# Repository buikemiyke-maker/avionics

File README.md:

# avionics
simple flight controller
the BOM can be found in the production folder
and also the code in the code folder
This took around a month and Im pretty unsure about some of my work so feel free to ask for any tweaks and Ill try to deliver asap 
The bills for parts I need, I will be uploading this onto the blueprint site aswell

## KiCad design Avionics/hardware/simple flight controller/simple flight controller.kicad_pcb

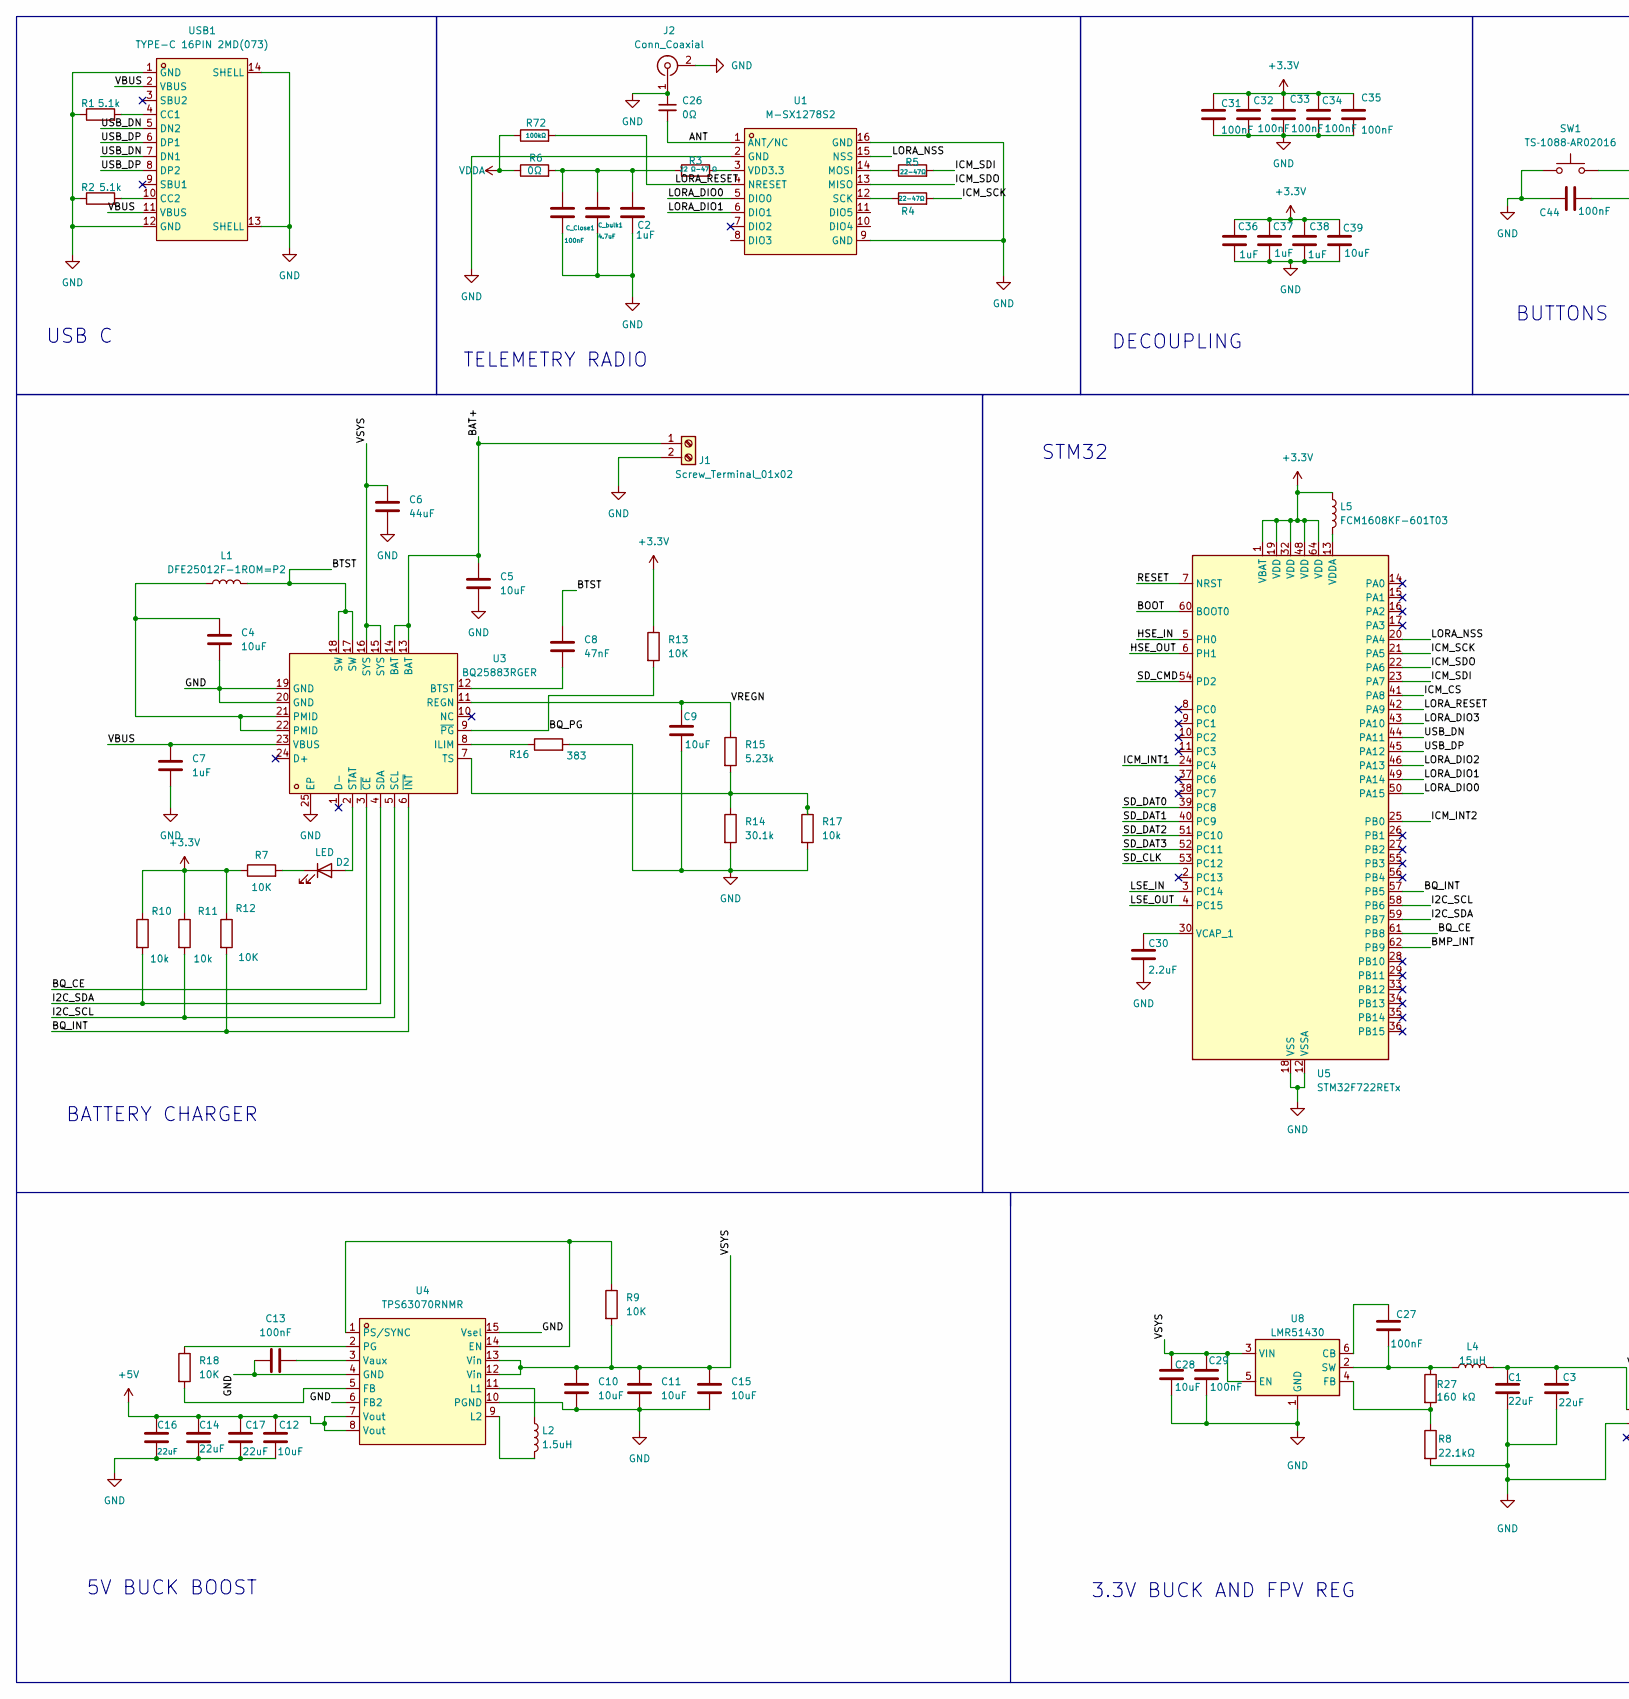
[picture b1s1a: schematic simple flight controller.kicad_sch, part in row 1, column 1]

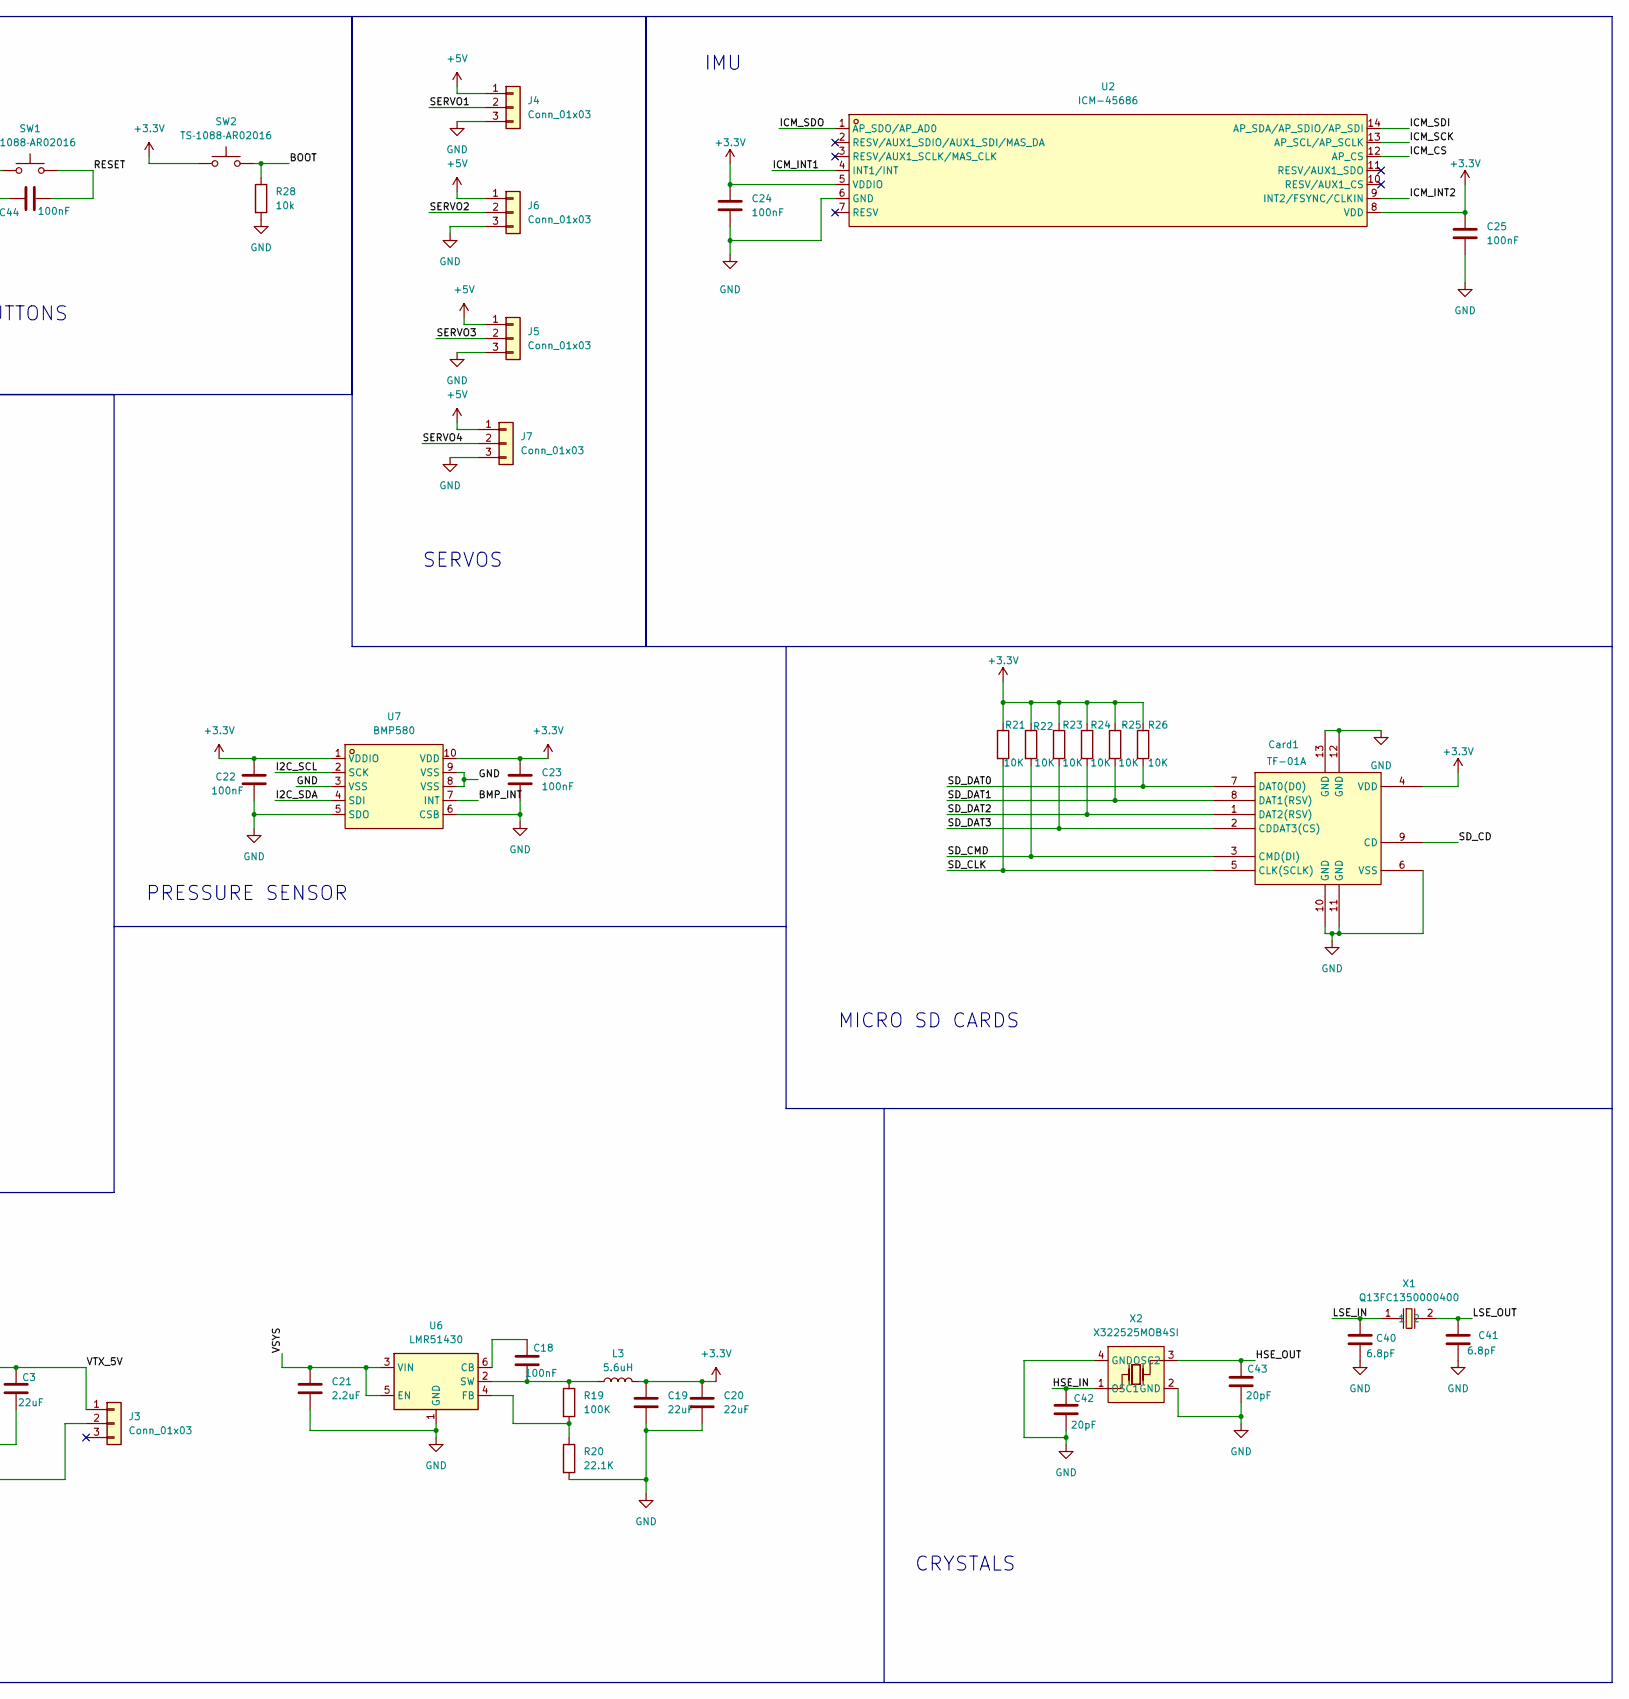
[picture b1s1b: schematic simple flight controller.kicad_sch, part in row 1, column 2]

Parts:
C1, C3, C14, C16, C17, C19, C20: 22uF; C_0805_2012Metric
C2, C7, C36, C37, C38: 1uF; C_0603_1608Metric
C4, C5, C9, C10, C11, C12, C15, C28, C39: 10uF; C_0805_2012Metric
C6: 44uF; C_1206_3216Metric
C8: 47nF; C_0603_1608Metric
C13: 100nF; C_0805_2012Metric
C18, C22, C23, C24, C25, C27, C29, C31, C32, C33, C34, C35, C44: 100nF; C_0603_1608Metric
C21, C30: 2.2uF; C_0603_1608Metric
C26: 0Ω; R_0603_1608Metric
C40, C41: 6.8pF; C_0603_1608Metric
C42, C43: 20pF; C_0603_1608Metric
C_Close1: 100nF; C_0603_1608Metric
C_bulk1: 4.7uF; C_0805_2012Metric
Card1: TF-01A; TF-SMD_TF-01A; LCSC Part C91145
D2: LED; LED_0402_1005Metric
J1: Screw_Terminal_01x02; TerminalBlock_Xinya_XY308-2.54-2P_1x02_P2.54mm_Horizontal
J2: Conn_Coaxial; U.FL_Hirose_U.FL-R-SMT-1_Vertical
J3, J4, J5, J6, J7: Conn_01x03; PinHeader_2x03_P2.54mm_Horizontal
L1: DFE25012F-1ROM=P2; L_1008_2520Metric
L2: 1.5uH; IND-SMD_L4.0-W4.0-A
L3: 5.6uH; IND-SMD_L3.0-W3.0
L4: 15uH; L_0603_1608Metric
L5: FCM1608KF-601T03; L0603
R1, R2: 5.1k; R_0201_0603Metric
R3: 22 Ω-47 Ω; R_0201_0603Metric
R4, R5: 22-47Ω; R_0201_0603Metric
R6: 0Ω; R_0201_0603Metric
R7, R9, R12, R13, R18, R21, R22, R23, R24, R25, R26: 10K; R_0201_0603Metric
R8: 22.1kΩ; R_0201_0603Metric
R10, R11, R17, R28: 10k; R_0201_0603Metric
R14: 30.1k; R_0201_0603Metric
R15: 5.23k; R_0201_0603Metric
R16: 383; R_0201_0603Metric
R19: 100K; R_0402_1005Metric
R20: 22.1K; R_0201_0603Metric
R27: 160 kΩ; R_0402_1005Metric
R72: 100kΩ; R_0402_1005Metric
SW1, SW2: TS‑1088‑AR02016; SW_PUSH_6mm
U1: M-SX1278S2; WIRELM-SMD_M-SX1278S2; LCSC Part C845532
U2: ICM-45686; LGA-14_L3.0-W2.5-P0.50-TL; LCSC Part C22459454
U3: BQ25883RGER; VFQFPN-24_L4.0-W4.0-P0.50-BL-EP2.8; LCSC Part C544362
U4: TPS63070RNMR; TPS63070_VQFN15_3x2mm; LCSC Part C109322
U5: STM32F722RETx; LQFP-64_10x10mm_P0.5mm
U6, U8: LMR51430; SOT-23-6
U7: BMP580; LGA-10_L2.0-W2.0-P0.50-TL_BMP580; LCSC Part C22391138
USB1: TYPE-C 16PIN 2MD(073); USB-C-SMD_TYPE-C-6PIN-2MD-073; LCSC Part C2765186
X1: Q13FC1350000400; FC-135R_L3.2-W1.5; LCSC Part C32346
X2: X322525MOB4SI; CRYSTAL-SMD_4P-L3.2-W2.5-BL; LCSC Part C9006

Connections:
+3.3V: C19.1, C20.1, C22.1, C23.1, C24.1, C25.1, C31.1, C32.1, C33.1, C34.1, C35.1, C36.1, C37.1, C38.1, C39.1, Card1.4 (VDD), L3.2, L5.1, R7.1, R10.1, R11.1, R12.1, R13.1, R21.1, R22.1, R23.1, R24.1, R25.1, R26.1, SW2.1, U2.5 (VDDIO), U2.8 (VDD), U5.1 (VBAT), U5.19 (VDD), U5.32 (VDD), U5.48 (VDD), U5.64 (VDD), U7.1 (VDDIO), U7.10 (VDD)
+5V: C12.1, C14.1, C16.1, C17.1, J4.1, J5.1, J6.1, J7.1, U4.7 (Vout), U4.8 (Vout)
/ANT: C26.2, U1.1 (ANT/NC)
/BAT+: C5.1, J1.1, U3.13 (BAT), U3.14 (BAT)
/BMP_INT: U5.62 (PB9), U7.7 (INT)
/BOOT: R28.1, SW2.2, U5.60 (BOOT0)
/BQ_CE: U3.3 (~CE), U5.61 (PB8)
/BQ_INT: R12.2, U3.6 (~INT), U5.57 (PB5)
/BQ_PG: R13.2, U3.9 (~PG)
/BTST: C8.1, L1.2, U3.17 (SW), U3.18 (SW)
/HSE_IN: C42.1, U5.5 (PH0), X2.1 (OSC1)
/HSE_OUT: C43.1, U5.6 (PH1), X2.3 (OSC2)
/I2C_SCL: R11.2, U3.5 (SCL), U5.58 (PB6), U7.2 (SCK)
/I2C_SDA: R10.2, U3.4 (SDA), U5.59 (PB7), U7.4 (SDI)
/ICM_CS: U2.12 (AP_CS), U5.41 (PA8)
/ICM_INT1: U2.4 (INT1/INT), U5.24 (PC4)
/ICM_INT2: U2.9 (INT2/FSYNC/CLKIN), U5.25 (PB0)
/ICM_SCK: R4.2, U2.13 (AP_SCL/AP_SCLK), U5.21 (PA5)
/ICM_SDI: R5.2, U2.14 (AP_SDA/AP_SDIO/AP_SDI), U5.23 (PA7)
/ICM_SDO: U1.13 (MISO), U2.1 (AP_SDO/AP_AD0), U5.22 (PA6)
/LORA_DIO0: U1.5 (DIO0), U5.50 (PA15)
/LORA_DIO1: U1.6 (DIO1), U5.49 (PA14)
/LORA_DIO2: U5.46 (PA13)
/LORA_DIO3: U5.43 (PA10)
/LORA_NSS: U1.15 (NSS), U5.20 (PA4)
/LORA_RESET: R72.2, U1.4 (NRESET), U5.42 (PA9)
/LSE_IN: C40.1, U5.3 (PC14), X1.1
/LSE_OUT: C41.1, U5.4 (PC15), X1.2
/RESET: C44.2, SW1.2, U5.7 (NRST)
/SD_CD: Card1.9 (CD)
/SD_CLK: Card1.5 (CLK(SCLK)), R21.2, U5.53 (PC12)
/SD_CMD: Card1.3 (CMD(DI)), R22.2, U5.54 (PD2)
/SD_DAT0: Card1.7 (DAT0(D0)), R26.2, U5.39 (PC8)
/SD_DAT1: Card1.8 (DAT1(RSV)), R25.2, U5.40 (PC9)
/SD_DAT2: Card1.1 (DAT2(RSV)), R24.2, U5.51 (PC10)
/SD_DAT3: Card1.2 (CDDAT3(CS)), R23.2, U5.52 (PC11)
/SERVO1: J4.2
/SERVO2: J6.2
/SERVO3: J5.2
/SERVO4: J7.2
/USB_DN: U5.44 (PA11), USB1.5 (DN2), USB1.7 (DN1)
/USB_DP: U5.45 (PA12), USB1.6 (DP1), USB1.8 (DP2)
/VBUS: C7.1, U3.23 (VBUS), USB1.2 (VBUS), USB1.11 (VBUS)
/VREGN: C9.1, R15.1, U3.11 (REGN)
/VSYS: C6.1, C10.1, C11.1, C15.1, C21.1, C28.1, C29.1, R9.2, U3.15 (SYS), U3.16 (SYS), U4.12 (Vin), U4.13 (Vin), U6.3 (VIN), U6.5 (EN), U8.3 (VIN), U8.5 (EN)
/VTX_5V: C1.1, C3.1, J3.1, L4.2
GND: C1.2, C2.2, C3.2, C4.2, C5.2, C6.2, C7.2, C9.2, C10.2, C11.2, C12.2, C13.1, C14.2, C15.2, C16.2, C17.2, C19.2, C20.2, C21.2, C22.2, C23.2, C24.2, C25.2, C26.1, C28.2, C29.2, C30.2, C31.2, C32.2, C33.2, C34.2, C35.2, C36.2, C37.2, C38.2, C39.2, C40.2, C41.2, C42.2, C43.2, C44.1, C_Close1.2, C_bulk1.2, Card1.6 (VSS), Card1.10 (GND), Card1.11 (GND), Card1.12 (GND), Card1.13 (GND), J1.2, J2.1 (In), J2.2 (Ext), J3.2, J4.3, J5.3, J6.3, J7.3, R1.1, R2.1, R8.2, R14.2, R16.2, R17.2, R20.2, R28.2, SW1.1, U1.2 (GND), U1.9 (GND), U1.16 (GND), U2.6 (GND), U3.19 (GND), U3.20 (GND), U3.25 (EP), U4.4 (GND), U4.6 (FB2), U4.10 (PGND), U4.15 (Vsel), U5.12 (VSSA), U5.18 (VSS), U5.31 (VSS), U5.47 (VSS), U5.63 (VSS), U6.1 (GND), U7.3 (VSS), U7.5 (SDO), U7.6 (CSB), U7.8 (VSS), U7.9 (VSS), U8.1 (GND), USB1.1 (GND), USB1.12 (GND), USB1.13 (SHELL), USB1.14 (SHELL), X2.2 (GND), X2.4 (GND)
unnamed: C2.1, C_Close1.1, C_bulk1.1, R3.1, R6.2
unnamed: C4.1, L1.1, U3.21 (PMID), U3.22 (PMID)
unnamed: D2.2 (A), U3.2 (STAT)
unnamed: D2.1 (K), R7.2
unnamed: R5.1, U1.14 (MOSI)
unnamed: R4.1, U1.12 (SCK)
unnamed: R3.2, U1.3 (VDD3.3)
unnamed: C8.2, U3.12 (BTST)
unnamed: R16.1, U3.8 (ILIM)
unnamed: R14.1, R15.2, R17.1, U3.7 (TS)
unnamed: R9.1, U4.1 (PS/SYNC), U4.14 (EN)
unnamed: R18.2, U4.5 (FB)
unnamed: L2.1, U4.11 (L1)
unnamed: L2.2, U4.9 (L2)
unnamed: R18.1, U4.2 (PG)
unnamed: C13.2, U4.3 (Vaux)
unnamed: C30.1, U5.30 (VCAP_1)
unnamed: L5.2, U5.13 (VDDA)
unnamed: C18.1, U6.6 (CB)
unnamed: R19.2, R20.1, U6.4 (FB)
unnamed: C18.2, L3.1, R19.1, U6.2 (SW)
unnamed: C27.1, U8.6 (CB)
unnamed: R8.1, R27.2, U8.4 (FB)
unnamed: C27.2, L4.1, R27.1, U8.2 (SW)
unnamed: R1.2, USB1.4 (CC1)
unnamed: R2.2, USB1.10 (CC2)
VDDA: R6.1, R72.1

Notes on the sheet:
IMU
CRYSTALS
3.3V BUCK AND FPV REG
BUTTONS
BATTERY CHARGER
USB C
SERVOS
5V BUCK BOOST
DECOUPLING
STM32
MICRO SD CARDS
PRESSURE SENSOR
TELEMETRY RADIO

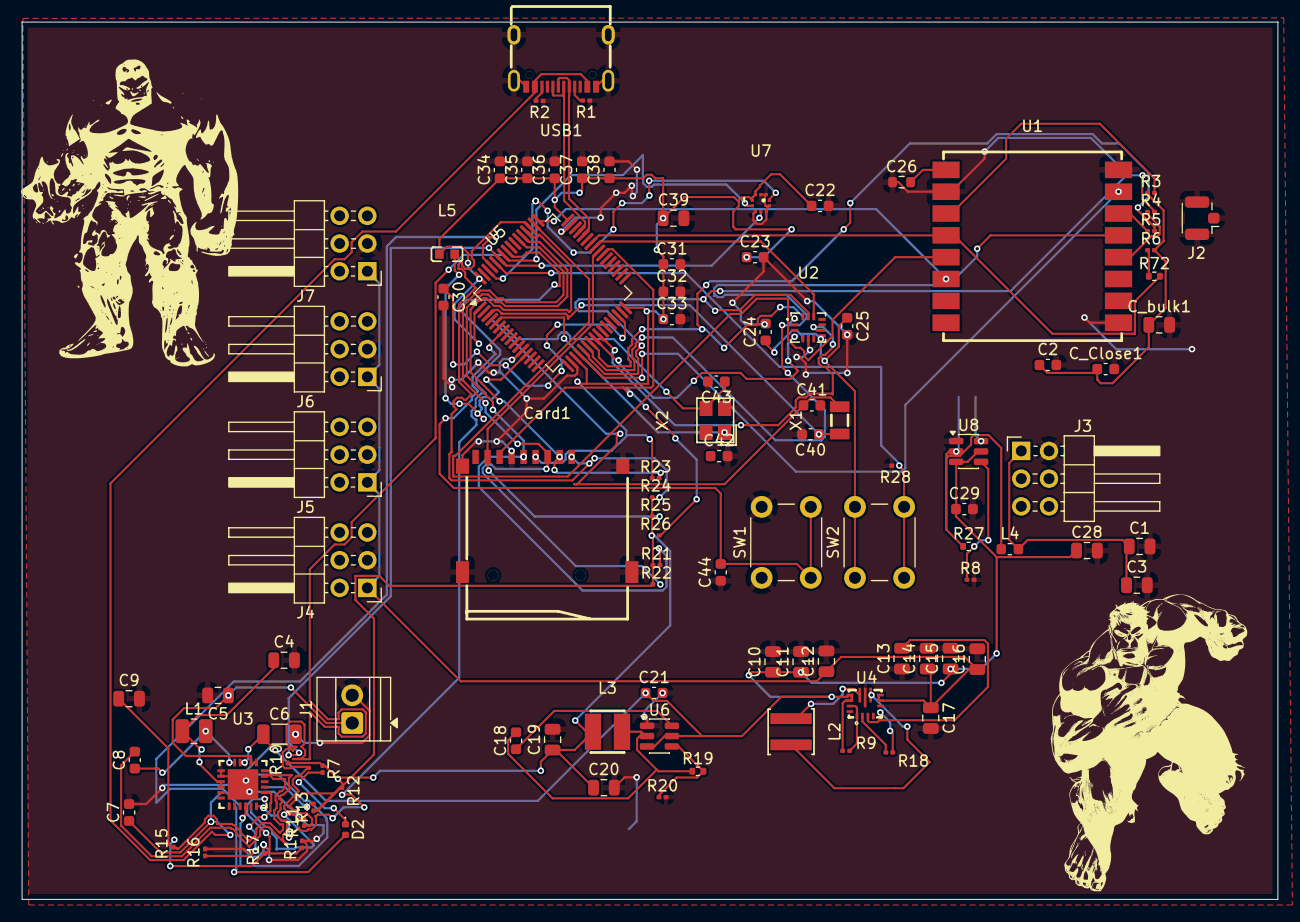
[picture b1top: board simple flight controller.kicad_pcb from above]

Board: 2 copper layers, 115.1 x 80.4 mm, 102 parts (1 on the bottom side), 67 nets.

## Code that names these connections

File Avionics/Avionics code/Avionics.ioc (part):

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Mcu.Name=STM32F722R(C-E)Tx
Mcu.Package=LQFP64
Mcu.UserName=STM32F722RETx
PA0-WKUP.Signal=S_TIM2_CH1_ETR
PA1.Signal=S_TIM2_CH2
PA10.GPIOParameters=GPIO_Label
PA10.GPIO_Label=LORA_DIO3
PA10.Signal=GPIO_Input
PA11.Mode=Host_Only
PA11.Signal=USB_OTG_FS_DM
PA12.Mode=Host_Only
PA12.Signal=USB_OTG_FS_DP
PA13.GPIOParameters=GPIO_Label
PA13.GPIO_Label=LORA_DIO2
PA13.Signal=GPIO_Input
PA14.GPIOParameters=GPIO_Label,GPIO_Mode
PA14.GPIO_Label=LORA_DIO1
PA14.GPIO_Mode=GPIO_MODE_INPUT
PA14.Signal=GPIO_Input
PA15.GPIOParameters=GPIO_Label
PA15.GPIO_Label=LORA_DIO0
PA15.Signal=GPXTI15
PA4.GPIOParameters=PinState,GPIO_Label
PA4.GPIO_Label=LORA_NSS
PA4.PinState=GPIO_PIN_SET
PA4.Signal=GPIO_Output
PA5.Mode=Full_Duplex_Master
PA5.Signal=SPI1_SCK
PA6.Mode=Full_Duplex_Master
PA6.Signal=SPI1_MISO
PA7.Mode=Full_Duplex_Master
PA7.Signal=SPI1_MOSI
PA9.GPIOParameters=PinState,GPIO_Label
PA9.GPIO_Label=LORA_RESET
PA9.PinState=GPIO_PIN_SET
PA9.Signal=GPIO_Output
PB0.GPIOParameters=GPIO_Label
PB0.GPIO_Label=ICM_INT2
PB0.Signal=GPXTI0
PB3.GPIOParameters=GPIO_Label
PB3.GPIO_Label=SD_CS
PB3.Signal=GPIO_Input
PB5.GPIOParameters=GPIO_Label
PB5.GPIO_Label=BQ_INT
PB5.Signal=GPXTI5
PB6.Mode=I2C
PB6.Signal=I2C1_SCL
PB7.Mode=I2C
PB7.Signal=I2C1_SDA
PB8.GPIOParameters=GPIO_Label
PB8.GPIO_Label=BQ_CE
PB8.Signal=GPIO_Output
PB9.GPIOParameters=GPIO_Label
PB9.GPIO_Label=BMP_INT
PB9.Signal=GPXTI9
PC10.Mode=SD_4_bits_Wide_bus
PC10.Signal=SDMMC1_D2
PC11.Mode=SD_4_bits_Wide_bus
PC11.Signal=SDMMC1_D3
PC12.Mode=SD_4_bits_Wide_bus
PC12.Signal=SDMMC1_CK
PC14-OSC32_IN.Mode=LSE-External-Oscillator
PC14-OSC32_IN.Signal=RCC_OSC32_IN
PC15-OSC32_OUT.Mode=LSE-External-Oscillator
PC15-OSC32_OUT.Signal=RCC_OSC32_OUT
PC4.GPIOParameters=GPIO_Label
PC4.GPIO_Label=ICM_INT1
PC4.Signal=GPXTI4
PC8.Mode=SD_4_bits_Wide_bus
PC8.Signal=SDMMC1_D0
PC9.Mode=SD_4_bits_Wide_bus
PC9.Signal=SDMMC1_D1
PD2.Mode=SD_4_bits_Wide_bus
PD2.Signal=SDMMC1_CMD
PH0-OSC_IN.Mode=HSE-External-Oscillator
PH0-OSC_IN.Signal=RCC_OSC_IN
PH1-OSC_OUT.Mode=HSE-External-Oscillator
PH1-OSC_OUT.Signal=RCC_OSC_OUT
RCC.HSE_VALUE=25000000
board=custom

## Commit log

2026-03-31 Files
